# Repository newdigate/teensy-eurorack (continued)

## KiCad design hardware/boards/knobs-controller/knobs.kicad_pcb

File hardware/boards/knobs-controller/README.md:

# Knobs Controller

```
status:
   01 Sept 2019: pcb delivery failure, pcbs re-ordered
   13 Dec 2019: 
     * v1.6: issue with tx/rx connection to mainboard fixed
```
## credits
* this board is based on [Arduino MKR Zero](https://store.arduino.cc/arduino-mkr-zero-i2s-bus-sd-for-sound-music-digital-audio-data) design by Arturo Guadalupi (v5.0)

## build
* build details for knob controller can be found here - [BUILD.md](BUILD.md) 
* BOM can be found here [Bill-of-materials.md](Bill-of-materials.md)

## quick details
An independent rotary encoder and potentiometer breakout board based on Arduino MKR Zero
* SAMD21G18A-MU 32bit micro-controller @ 48 MHz. 
* 4 x 12bit rotary potentiometers
* 3 x RGB Illuminated rotary encoder w/ switch
* Communicates with main-board via serial rx / tx

## objectives
Introducing an intermediate micro-controller (ARM cortex M0 / SAMD21G) 
* reduces complexity of mainboard
* reduces number of anlog and digital pins required by teensy for haptic input (knobs and pots)
* simplyfies and unifies mainboard firmware for 

some firmware will run on the M0 microcontroller to relay input (knob value changes) back to the mainboard and receive commands (eg. to light up RGB rotaries ) via serial TX / RX, 

Number of signal required between main-board and knobs controller is reduced to: +5V, GND, TX, RX; 
## revisions
* v1.5: board size reduced slightly on the right hand side to allow assembly to fit in to a 6U high rack mount unit.
* v1.6: 
  * fixed tx/rx connection
  * moved connector to mainboard out of the way

## todo 
- [ ] change mcu to ATSAMD21G18A-AU (jlc pcb assembly friendly)

## How did this happen?
I want to upgrade the mainboard to using a teensy 4.0 and I don't want to rely on using the pins on the underside of the teensy. 

I started with the schematic of [arduino mkr zero](https://create.arduino.cc/projecthub/products/arduino-mkr-zero) (available from arduino -- [MKRZero-reference.zip](https://content.arduino.cc/assets/MKRZero-reference.zip) as eagle .sch and .brd) and removed components from the circuit which I don't need. I needed to keep the SWD (Serial wire debug) pins on the micro-controller available, so I can upload a bootloader- as the usb connection won't be available until the bootloader is programmed via the 6-pin SWD header.

## Images

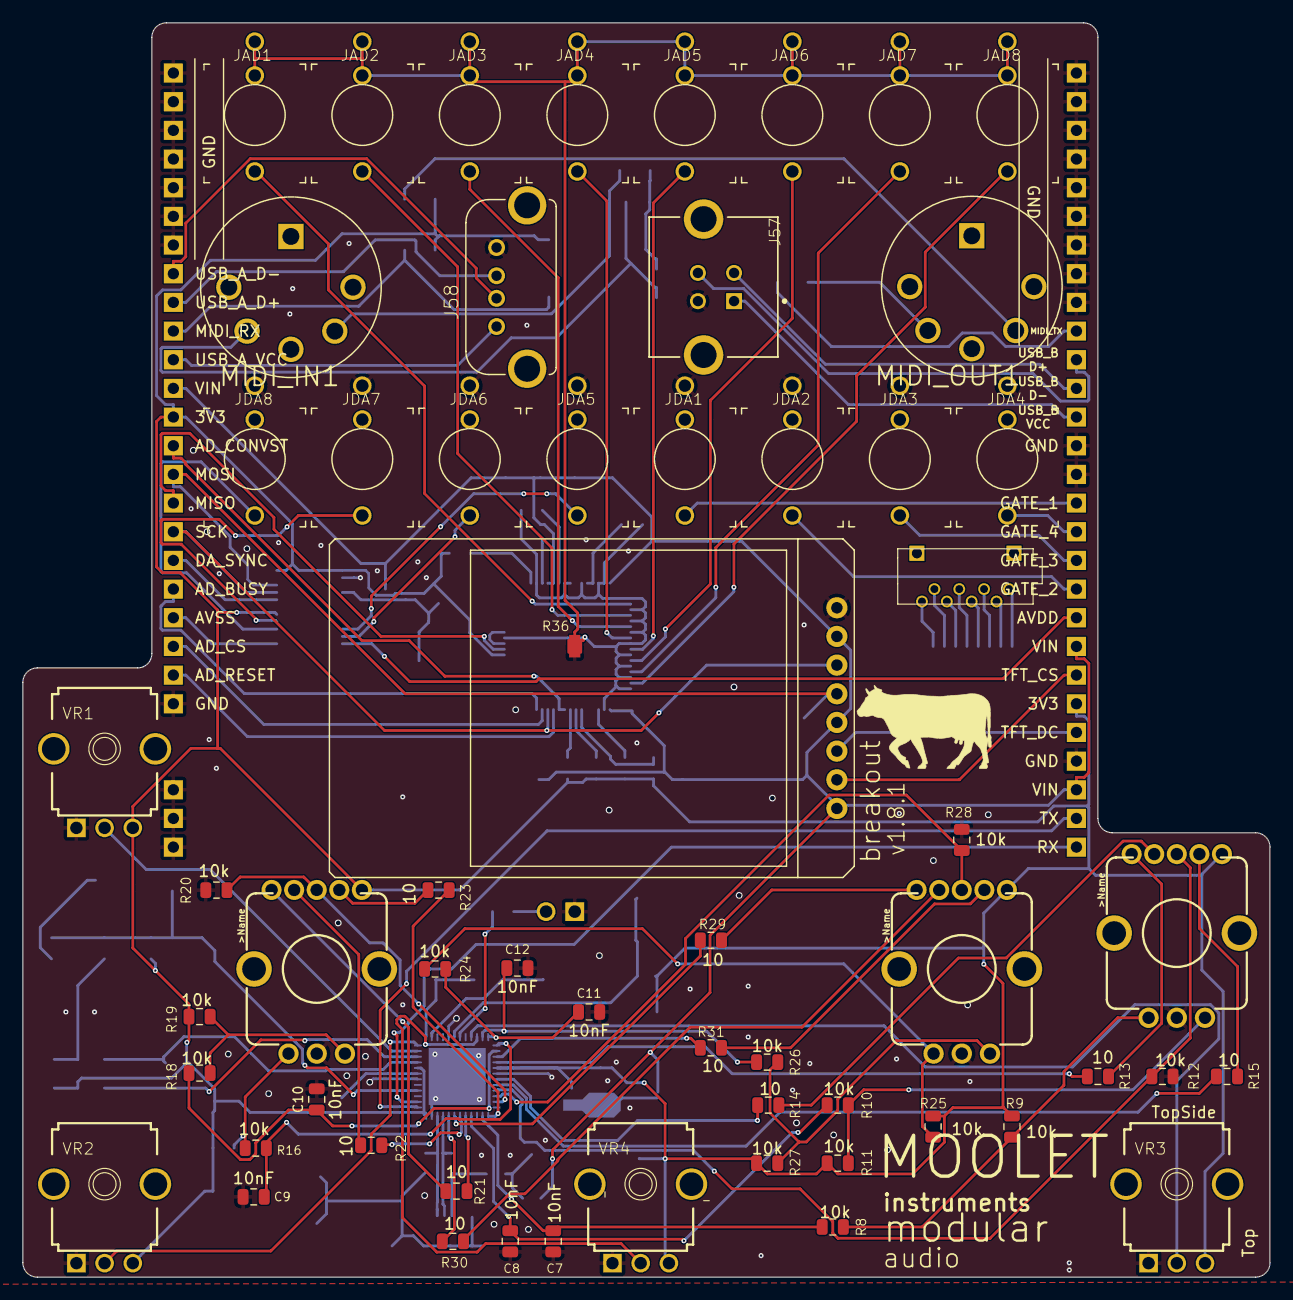
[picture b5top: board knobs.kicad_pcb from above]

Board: 2 copper layers, 110.5 x 111.1 mm, 175 parts (0 on the bottom side), 117 nets.

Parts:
C1: 4.7nF; C_0805_2012Metric
C2, C6: 1nF; C_0805_2012Metric
C3, C13, C15, C16, C17, C21, C22, C23, C24, C28, C29, C30, C31: 0.1uF; C_0805_2012Metric
C4, C5: 20pF; C_0805_2012Metric
C7, C8, C9, C10, C11, C12: 10nF; C_0805_2012Metric
C14, C19, C20, C26, C27: 1uF; C_0805_2012Metric
C18: 4.7uF; C_0805_2012Metric
C25: 10uF; C_0805_2012Metric
D1: PRTR5V0U2X,215; MK1_ZERO_SOT190P230X110-4N
D2: LED; LED_RADIAL_3MM
D3: D; D_0805
F1: MF-FSMF050X-2; MK1_ZERO_0603-F1608X100N
J1: ZX62-AB-5PA(31); MK1_ZERO_USBMICRO-ZX62-AB-5PA
J2: 2X3_SMD_MALE; 2X3_SMT
J3, J4, J5, J6, J7, J8, J9, J10, J11, J12, J13, J14, J15, J16, J17, J18, J19, J20, J21, J22, J23, J24, J25, J26, J27, J28, J29, J30, J31, J32, J33, J34, J35, J36, J37, J38, J39, J40, J41, J42, J43, J44, J45, J46, J47, J48, J49, J50, J51, J52, J53, J54, J55, J56: Conn_01x01_Female; PinSocket_1x01_P2.54mm_Vertical
J57: WURTH_ELECTRONICS_61400413321WURTH_ELECTRONICS_61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; WURTH_ELECTRONICS_61400413321_0
J58: USB-A-S-X-X-VT
J59: ST7735_1.4; ST7735
JAD1, JAD2, JAD3, JAD4, JAD5, JAD6, JAD7, JAD8: THONKICONNNEW; WQP-PJ301M-12_JACK
JDA1, JDA2, JDA3, JDA4, JDA5, JDA6, JDA7, JDA8: THONKICONNNEW; WQP-PJ301M-12_JACK
L1, L2: BLM18PG471SN1D; MK1_ZERO_0603-1608X90N
MIDI_IN1: OG-MIDI_MAB5SHCUI-SD-50BV; OG-MIDI_SD-50BV
MIDI_OUT1: OG-MIDI_MAB5SHCUI-SD-50BV; OG-MIDI_SD-50BV
R1: 1M; R_0805_2012Metric
R2: 39R; R_0805_2012Metric
R3, R6, R7: 330R; R_0805_2012Metric
R4: 1k; R_0805_2012Metric
R5, R8, R9, R10, R11, R12, R16, R17, R18, R19, R20, R24, R25, R26, R27, R28: 10k; R_0805_2012Metric
R13, R14, R15, R21, R22, R23, R29, R30, R31: 10; R_0805_2012Metric
R32, R33, R34, R35, R37: 4.7k; R_0805
R36: 0; NetTie-I_Connected_SMD_small
R38, R39, R40, R41: 220; R_0805_HandSoldering
SW1, SW2, SW3: Rotary Encoder; ENCODER_LED_3_KIT
TP1, TP2, TP3: TEST-POINT3X5; PAD.03X.05
U1: ATSAMD21G18A-48; MK1_ZERO_QFN50P700X700X90-49XN-EPSQ515
U2: AP7215-33YG-13; MK1_ZERO_SOT150P400X160-3N
U3: ANALOG_DEVICES_AD7606BSTZANALOG_DEVICES_AD7606BST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; ANALOG_DEVICES_AD7606BSTZ_2
U4: ANALOG_DEVICES_AD5754BREZANALOG_DEVICES_AD5754BRE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; ANALOG_DEVICES_AD5754BREZ_2
U5: MICROCHIP_MCP1700T-2502E-TTMICROCHIP_MCP1700T-250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; MICROCHIP_MCP1700T-2502E-TT_0
U$1: PUSHBUTTON2; C&K_PTS820_NOPEGS
U$2: YAMAICHI_SD_CARD; YAMAICHI_MICROSD_VERTICAL
U$3: 1734592-8; HFW8R-1STE1LF
U$4: OPTO_DARL_6N138S; 8-SMD
VR1, VR2, VR3, VR4: 50k; MUSICTHINGMODULAR_9MM_SNAP-IN_POT
Y1: 32.768KHz; MK1_ZERO_QUARZO-ABS07

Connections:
+3V3: C13.1, C15.1, C16.1, C20.1, J2.1, J40.1, J41.1, L2.1, R4.2, R5.2, R9.2, R11.1, R17.2, R19.1, R25.2, R27.1, R32.1, R33.1, R34.2, R35.1, R37.2, R38.2, R41.2, SW1.5, SW2.5, SW3.5, U1.17, U1.36, U1.44, U2.3, U3.23, U4.5, U4.11, U4.14, U$4.8, VR1.3, VR2.3, VR3.3, VR4.3
/AD5754 DAC/VREF: C30.1, C31.1, TP3.P$1, U4.17, U5.2
/AD7606/AD_BYTE_SELECT: R33.2, U3.6
/AD7606/AD_OS0: R35.2, U3.3
/AD7606/AD_RANGE: R32.2, U3.8
/AD7606/AD_REFCAP_A: C25.1, U3.44, U3.45
/AD7606/AD_REFSEL: R37.1, U3.34
/AD7606/AD_REGCAP1: C26.1, U3.36
/AD7606/AD_REGCAP2: C27.1, U3.39
/AD7606/AD_STBY: R34.1, U3.7
/FPC connector/SD_CLK: U$2.P$5, U$3.4
/FPC connector/SD_CS: U$2.P$2, U$3.7
/FPC connector/SD_DAT1: U$2.P$8, U$3.1
/FPC connector/SD_DAT2: U$2.P$1, U$3.8
/FPC connector/SD_DATAIN: U$2.P$3, U$3.6
/FPC connector/SD_DATAOUT: U$2.P$7, U$3.2
/FPC connector/SD_GND: U$2.P$6, U$3.3
/FPC connector/SD_VCC: U$2.P$4, U$3.5
/FPC connector/USB_A_D+: J30.1, J58.3
/FPC connector/USB_A_D-: J31.1, J58.2
/FPC connector/USB_A_VCC: J32.1, J58.1
/FPC connector/USB_B_D+: J27.1, J57.3
/FPC connector/USB_B_D-: J28.1, J57.2
/FPC connector/USB_B_VCC: J29.1, J57.1
/knobs_1/PA00_XIN32: C4.2, U1.1, Y1.2
/knobs_1/PA01_XOUT32: C5.2, U1.2, Y1.1
/knobs_1/PA04_AIN4: U1.9, VR3.2
/knobs_1/PA05_AIN5: U1.10, VR4.2
/knobs_1/PA06_AIN6: C12.1, R26.1, U1.11
/knobs_1/PA07_AIN7: C11.1, R24.2, U1.12
/knobs_1/PA08_S0_I2C_SDA: C9.1, R16.2, U1.13
/knobs_1/PA09_S0_I2C_SCL: C10.1, R18.1, U1.14
/knobs_1/PA10_TCC0-W2: R31.2, U1.15
/knobs_1/PA11_TCC0-W3: R13.2, U1.16
/knobs_1/PA12_S2_MOSI: R12.2, SW1.3, U1.21
/knobs_1/PA13_S2_SCK: R28.2, SW3.3, U1.22
/knobs_1/PA14_S2_NSS: R20.2, SW2.3, U1.23
/knobs_1/PA16_S1_MOSI: R23.2, U1.25
/knobs_1/PA17_S1_SCK: C7.1, R8.2, U1.26
/knobs_1/PA19_S1_MISO: C8.1, R10.1, U1.28
/knobs_1/PA20_TCC0-W6: R21.2, U1.29
/knobs_1/PA21_TCC0-W7: R22.2, U1.30
/knobs_1/PA22_TC4-W0: R29.2, U1.31
/knobs_1/PA23_TC4-W1: R30.2, U1.32
/knobs_1/PA30_SWCLK: J2.4, R4.1, U1.45
/knobs_1/PA31_SWDIO: J2.2, U1.46
/knobs_1/PB02_AIN10: U1.47, VR1.2
/knobs_1/PB03_AIN11: U1.48, VR2.2
/knobs_1/PB08_LED: R7.1, U1.7
/knobs_1/PB10_TCC0-W4: R14.2, U1.19
/knobs_1/PB11_TCC0-W5: R15.2, U1.20
/knobs_1/PB22_S5_TX: J5.1, U1.37
/knobs_1/PB23_S5_RX: J4.1, U1.38
/knobs_1/RESETN: C3.1, R2.2, R3.2, R5.1, R6.1, U1.40
/knobs_1/USB_N: D1.3, J1.2, U1.33
/knobs_1/USB_P: D1.2, J1.3, U1.34
AD_AGND: C25.2, C26.2, C27.2, JAD1.P$2_SWITCH, JAD1.P$3_SLEEVE, JAD2.P$2_SWITCH, JAD2.P$3_SLEEVE, JAD3.P$2_SWITCH, JAD3.P$3_SLEEVE, JAD4.P$2_SWITCH, JAD4.P$3_SLEEVE, JAD5.P$2_SWITCH, JAD5.P$3_SLEEVE, JAD6.P$2_SWITCH, JAD6.P$3_SLEEVE, JAD7.P$2_SWITCH, JAD7.P$3_SLEEVE, JAD8.P$2_SWITCH, JAD8.P$3_SLEEVE, R36.2, U3.2, U3.26, U3.35, U3.40, U3.41, U3.43, U3.46, U3.47, U3.50, U3.52, U3.54, U3.56, U3.58, U3.60, U3.62, U3.64
AD_BUSY: J52.1, U3.14
AD_CONVST: J53.1, U3.9, U3.10
AD_CS: J55.1, U3.13
AD_RESET: J54.1, U3.11
AD_V1: JAD1.P$1_TIP, U3.49
AD_V2: JAD2.P$1_TIP, U3.51
AD_V3: JAD3.P$1_TIP, U3.53
AD_V4: JAD4.P$1_TIP, U3.55
AD_V5: JAD5.P$1_TIP, U3.57
AD_V6: JAD6.P$1_TIP, U3.59
AD_V7: JAD7.P$1_TIP, U3.61
AD_V8: JAD8.P$1_TIP, U3.63
AVDD: J46.1, U4.24
AVSS: J47.1, U4.1
DA_SYNC: J36.1, U4.7
DA_V1: JDA8.P$1_TIP, U4.3
DA_V2: JDA7.P$1_TIP, U4.4
DA_V3: JDA6.P$1_TIP, U4.23
DA_V4: JDA5.P$1_TIP, U4.22
GATE_1: J42.1, JDA1.P$1_TIP
GATE_2: J43.1, JDA2.P$1_TIP
GATE_3: J44.1, JDA3.P$1_TIP
GATE_4: J45.1, JDA4.P$1_TIP
GND: C1.2, C2.2, C3.2, C4.1, C5.1, C6.2, C7.2, C8.2, C9.2, C10.2, C11.2, C12.2, C13.2, C14.2, C15.2, C16.2, C17.2, C18.2, C19.2, C20.2, C21.2, C22.2, C23.2, C24.2, C28.2, C29.2, C30.2, C31.2, D2.C, J1.5, J2.5, J3.1, J7.1, J8.1, J9.1, J10.1, J11.1, J12.1, J13.1, J14.1, J15.1, J16.1, J17.1, J18.1, J19.1, J20.1, J21.1, J22.1, J23.1, J24.1, J25.1, J26.1, J37.1, J56.1, J57.4, J58.4, J59.1, JDA1.P$3_SLEEVE, JDA2.P$3_SLEEVE, JDA3.P$3_SLEEVE, JDA4.P$3_SLEEVE, JDA5.P$3_SLEEVE, JDA6.P$3_SLEEVE, JDA7.P$3_SLEEVE, JDA8.P$3_SLEEVE, R1.1, R12.1, R20.1, R28.1, R36.1, SW1.C, SW2.C, SW3.C, U1.5, U1.18, U1.35, U1.42, U1.49, U2.1, U3.4, U3.5, U3.16, U3.17, U3.18, U3.19, U3.20, U3.21, U3.22, U3.25, U3.27, U3.28, U3.29, U3.30, U3.31, U3.32, U3.33, U4.10, U4.15, U4.18, U4.19, U4.20, U4.21, U5.1, U$1.1, U$1.2, U$1.3, U$1.4, U$1.5, U$4.5, VR1.1, VR2.1, VR3.1, VR4.1
MIDI_IN_PIN4: MIDI_IN1.4, R39.1
MIDI_IN_PIN5: D3.2, MIDI_IN1.5, U$4.3
MIDI_OUT_PIN4: MIDI_OUT1.4, R38.1
MIDI_OUT_PIN5: MIDI_OUT1.5, R40.1
MIDI_RX: J33.1, R41.1, U$4.6
MIDI_TX: J34.1, R40.2
unnamed: C1.1, D1.1, J1.6, J1.7, J1.8, J1.9, J1.10, J1.11, R1.2
unnamed: C2.1, F1.1, L1.1
unnamed: C14.1, U1.43
unnamed: C17.1, C18.1, L2.2, U1.6
unnamed: D1.4, F1.2, J1.1
unnamed: D2.A, R7.2
unnamed: D3.1, R39.2, U$4.2
unnamed: J2.3, R2.1
unnamed: R3.1, U$1.6
unnamed: R8.1, R9.1, SW1.A
unnamed: R10.2, R11.2, SW1.B
unnamed: R13.1, SW1.1
unnamed: R14.1, SW1.2
unnamed: R15.1, SW1.4
unnamed: R16.1, R17.1, SW2.A
unnamed: R18.2, R19.2, SW2.B
unnamed: R21.1, SW2.1
unnamed: R22.1, SW2.2
unnamed: R23.1, SW2.4
unnamed: R24.1, R25.1, SW3.A
unnamed: R26.2, R27.2, SW3.B
unnamed: R29.1, SW3.1
unnamed: R30.1, SW3.2
unnamed: R31.1, SW3.4
SPI0_MISO: J51.1, U3.24
SPI0_MOSI: J35.1, J59.4, TP2.P$1, U4.9
SPI0_SCK: J50.1, J59.3, U3.12, U4.8
TFT_CS: J49.1, J59.7
TFT_DC: J48.1, J59.6
VIN: C6.1, C19.1, C21.1, C22.1, C23.1, C24.1, C28.1, C29.1, J6.1, J38.1, J39.1, J59.2, J59.5, J59.8, L1.2, TP1.P$1, U2.2, U3.1, U3.37, U3.38, U3.48, U5.3

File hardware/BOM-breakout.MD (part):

| No | Qty | Reference(s)                                                                                   | Value                                                          | Footprint                     | Mfg. Part Number      |         |        |
|----|-----|------------------------------------------------------------------------------------------------|----------------------------------------------------------------|-------------------------------|-----------------------|---------|--------|
| 1  | 1   | C1                                                                                             | 4.7nF                                                          | 0805                          | C0805V472KDRACTU      | £0.181  | £0.18  |
| 2  | 2   | C2, C6                                                                                         | 1nF                                                            | 0805                          | C0805C102KARACAUTO    | £0.076  | £0.15  |
| 3  | 13  | C3, C13, C15, C16, C17, C21, C22, C23, C24, C28, C29, C30, C31                                 | 0.1uF                                                          | 0805                          | C0805C104J5RACTU      | £0.016  | £0.20  |
| 4  | 2   | C4, C5                                                                                         | 20pF                                                           | 0805                          | 1276-1829-1-ND        | £0.024  | £0.05  |
| 5  | 6   | C7, C8, C9, C10, C11, C12                                                                      | 10nF                                                           | 0805                          | C0805C103J5RACTU      | £0.014  | £0.08  |
| 6  | 5   | C14, C19, C20, C26, C27                                                                        | 1uF                                                            | 0805                          | C0805C105K4RACTU      | £0.027  | £0.14  |
| 7  | 1   | C18                                                                                            | 4.7uF                                                          | 0805                          | TAJP475K016RNJ        | £0.389  | £0.39  |
| 8  | 1   | C25                                                                                            | 10uF                                                           | 0805                          | LMK212ABJ106MG-T      | £0.028  | £0.03  |
| 9  | 1   | D1                                                                                             | PRTR5V0U2X,215                                                 | SOT190P230X110-4N             | PRTR5V0U2X,215        | £0.324  | £0.32  |
| 10 | 1   | D3                                                                                             | D                                                              | 0805                          | TS4148 RYG            | £0.020  | £0.02  |
| 11 | 1   | F1                                                                                             | MF-FSMF050X-2                                                  | 0603                          | MF-FSMF050X-2         | £0.543  | £0.54  |
| 12 | 1   | J1                                                                                             | ZX62-AB-5PA(31)                                                | USBMICRO-ZX62-AB-5PA          | ZX62-AB-5PA(31)       | £0.483  | £0.48  |
| 13 | 1   | J2                                                                                             | 2X3_SMD_MALE                                                   | 2X3_SMT                       | M20-8760342           | £0.239  | £0.24  |
| 14 | 1   | J57                                                                                            | WURTH_ELECTRONICS | 61400413321_0                 | 61400413321           | £0.909  | £0.91  |
| 15 | 1   | J58                                                                                            | USB-A-S-X-X-VT                                                 | USB-A-S-X-X-VT                | USB-A-S-S-W-VT        | £1.618  | £1.62  |
| 16 | 1   | J59                                                                                            | ST7735_1.4                                                     | ST7735                        | TFT ST7735 1.44"      | £2.690  | £2.69  |
| 17 | 16  | JAD1, JAD2, JAD3, JAD4, JAD5, JAD6, JAD7, JAD8, JDA1, JDA2, JDA3, JDA4, JDA5, JDA6, JDA7, JDA8 | THONKICONNNEW                                                  | WQP-PJ301M-12_JACK            | PJ398SM               | £0.298  | £4.76  |
| 18 | 2   | L1, L2                                                                                         | BLM18PG471SN1D                                                 | 0603                          | BLM18PG471SN1D        | £0.036  | £0.07  |
| 19 | 2   | MIDI_IN1, MIDI_OUT1                                                                            | OG-MIDI_MAB5SHCUI-SD-50BV                                      | SD-50BV                       | SD-50BV               | £1.033  | £2.07  |
| 20 | 1   | R1                                                                                             | 1M                                                             | 0805                          | CR0805-JW-105ELFCT-ND | £0.006  | £0.01  |
| 21 | 1   | R2                                                                                             | 39R                                                            | 0805                          | 804-6335              | £0.002  | £0.00  |
| 22 | 3   | R3, R6, R7                                                                                     | 330R                                                           | 0805                          | RMCF0805JT330R        | £0.007  | £0.02  |
| 23 | 1   | R4                                                                                             | 1K                                                             | 0805                          | 804-6449              | £0.002  | £0.00  |
| 24 | 16  | R5, R8, R9, R10, R11, R12, R16, R17, R18, R19, R20, R24, R25, R26, R27, R28                    | 10k                                                            | 0805                          | RR1220P-103-D         | £0.016  | £0.26  |
| 25 | 9   | R13, R14, R15, R21, R22, R23, R29, R30, R31                                                    | 10                                                             | 0805                          | RL1220S-100-F         | £0.135  | £1.21  |
| 26 | 5   | R32, R33, R34, R35, R37                                                                        | 4.7k                                                           | 0805                          | CRCW08054K70FKEAC     | £0.017  | £0.09  |
| 27 | 4   | R38, R39, R40, R41                                                                             | 220                                                            | 0805                          | CRCW0805220RFKEAC     | £0.014  | £0.06  |
| 28 | 3   | SW1, SW2, SW3                                                                                  | Rotary Encoder                                                 | ENCODER_LED_3_KIT             | COM-10982             | £3.250  | £9.75  |
| 29 | 1   | U1                                                                                             | ATSAMD21G18A-48                                                | QFN50P700X700X90-49XN | ATSAMD21G18A-MUT      | £2.370  | £2.37  |
| 30 | 1   | U2                                                                                             | AP7215-33YG-13                                                 | SOT150P400X160-3N             | AP7215-33YG-13DICT-ND | £0.349  | £0.35  |
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
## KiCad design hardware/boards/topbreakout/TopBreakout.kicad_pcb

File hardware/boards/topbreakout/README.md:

# Top breakout board

## Bill-of-materials

| Ref                                | Qnty | Value             | Cmp name           | Footprint                                 |
|------------------------------------|------|-------------------|--------------------|-------------------------------------------|
| C1, C2, C3, C4, C6, C9, C10, C11,  | 8    | 0.1u              | C-EUC0805K         | Capacitor_SMD:C_0805_2012Metric           |
| C5, C7,                            | 2    | 1.0uF             | 1.0UF-1206-50V-10% | Capacitor_SMD:C_0805_2012Metric           |
| C8,                                | 1    | 10uF              | 10UF-1206-6.3V-20% | Capacitor_SMD:C_0805_2012Metric           |
| D1,                                | 1    | D                 | D                  | Diodes_SMD:D_0805                         |
| R2, R5, R1, R3,                    | 4    | 220               | R-US_R0805         | Resistors_SMD:R_0805_HandSoldering        |
| R4, R7, R8, R9, R10,               | 5    | 4.7k              | R-US_R0805         | Resistors_SMD:R_0805                      |
| U1,                                | 1    | AD7606BSTZ        | AD7606BSTZ         | topbreakout:ANALOG_DEVICES_AD7606BSTZ_2   |
| U3,                                | 1    | AD5754BREZ        | AD5754BREZ         | topbreakout:ANALOG_DEVICES_AD5754BREZ_2   |
| U5,                                | 1    | MCP1700T-2502E-TT | MCP1700T-2502E-TT  | topbreakout:MICROCHIP_MCP1700T-2502E-TT_0 |
| U$1,                               | 1    | YAMAICHI_SD_CARD  | YAMAICHI_SD_CARD   | topbreakout:YAMAICHI_MICROSD_VERTICAL     |
| U$2,                               | 1    | 1734592-8         | 1734592-8          | common:HFW8R-1STE1LF                      |
| U$3,                               | 1    | OPTO_DARL_6N138S  | OPTO_DARL_6N138S   | Mainboard:8-SMD                           |

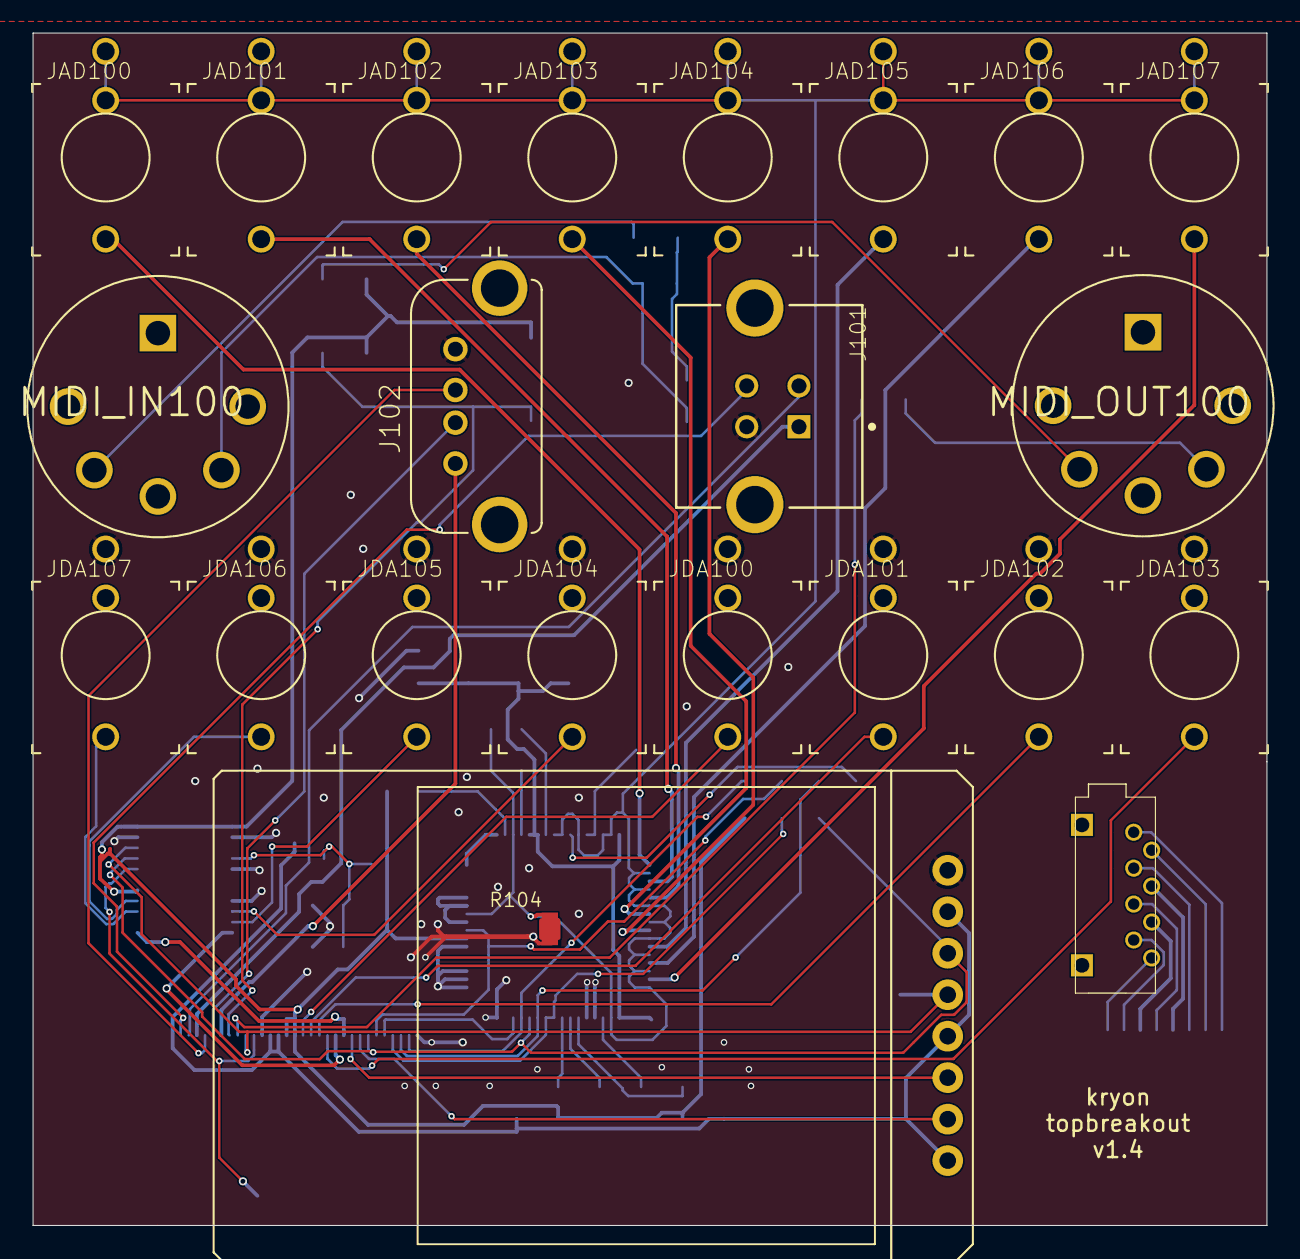
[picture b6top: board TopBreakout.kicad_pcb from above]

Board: 2 copper layers, 75.6 x 73.0 mm, 61 parts (0 on the bottom side), 64 nets.

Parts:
C100, C101, C102, C103: 0.1u; C0805K
C104: 10uF; C_0805_2012Metric
C105, C106: 1.0uF; C_0805_2012Metric
C107, C108: 0.1uF; C_0805
C109, C110: 0.1uF; C_0805_2012Metric
D100: D; D_0805
J100: MOLEX_52892-3033MOLEX_52892-3033_0_0; MOLEX_52892-3033_0
J101: WURTH_ELECTRONICS_61400413321WURTH_ELECTRONICS_61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; WURTH_ELECTRONICS_61400413321_0
J102: USB-A-S-X-X-VT
J103: ST7735_1.4; ST7735
JAD100, JAD101, JAD102, JAD103, JAD104, JAD105, JAD106, JAD107: THONKICONNNEW; WQP-PJ301M-12_JACK
JDA100, JDA101, JDA102, JDA103, JDA104, JDA105, JDA106, JDA107: THONKICONNNEW; WQP-PJ301M-12_JACK
MIDI_IN100: OG-MIDI_MAB5SHCUI-SD-50BV; OG-MIDI_SD-50BV
MIDI_OUT100: OG-MIDI_MAB5SHCUI-SD-50BV; OG-MIDI_SD-50BV
R100, R101, R102, R103, R105: 4.7k; R_0805
R104: 0; NetTie-I_Connected_SMD_small
R106, R107, R108, R109: 220; R_0805_HandSoldering
TP100, TP101, TP102, TP103, TP104, TP105, TP106, TP107, TP108, TP109, TP110: TEST-POINT3X5; PAD.03X.05
U100: ANALOG_DEVICES_AD7606BSTZANALOG_DEVICES_AD7606BST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; ANALOG_DEVICES_AD7606BSTZ_2
U101: ANALOG_DEVICES_AD5754BREZANALOG_DEVICES_AD5754BRE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; ANALOG_DEVICES_AD5754BREZ_2
U102: MICROCHIP_MCP1700T-2502E-TTMICROCHIP_MCP1700T-250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; MICROCHIP_MCP1700T-2502E-TT_0
U$100: YAMAICHI_SD_CARD; YAMAICHI_MICROSD_VERTICAL
U$101: 1734592-8; HFW8R-1STE1LF
U$102: OPTO_DARL_6N138S; 8-SMD

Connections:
+3V3: J100.16, J100.17, R100.1, R101.1, R102.2, R103.1, R105.2, R106.2, R109.2, TP102.P$1, U100.23, U101.5, U101.11, U101.14, U$102.8
/AD5754 DAC/VREF: C109.1, C110.1, TP110.P$1, U101.17, U102.2
/AD7606/AD_BYTE_SELECT: R101.2, U100.6
/AD7606/AD_OS0: R103.2, U100.3
/AD7606/AD_RANGE: R100.2, U100.8
/AD7606/AD_REFCAP_A: C104.1, U100.44, U100.45
/AD7606/AD_REFINOUT: TP107.P$1, U100.42
/AD7606/AD_REFSEL: R105.1, U100.34
/AD7606/AD_REGCAP1: C105.1, U100.36
/AD7606/AD_REGCAP2: C106.1, U100.39
/AD7606/AD_STBY: R102.1, U100.7
/AD7606/AVIN: C100.1, C101.1, C102.1, C103.1, TP100.P$1, U100.1, U100.37, U100.38, U100.48
/FPC connector/SD_CLK: U$100.P$5, U$101.4
/FPC connector/SD_CS: U$100.P$2, U$101.7
/FPC connector/SD_DAT1: U$100.P$8, U$101.1
/FPC connector/SD_DAT2: U$100.P$1, U$101.8
/FPC connector/SD_DATAIN: U$100.P$3, U$101.6
/FPC connector/SD_DATAOUT: U$100.P$7, U$101.2
/FPC connector/SD_GND: U$100.P$6, U$101.3
/FPC connector/SD_VCC: U$100.P$4, U$101.5
/FPC connector/USB_A_D+: J100.27, J102.3
/FPC connector/USB_A_D-: J100.26, J102.2
/FPC connector/USB_A_VCC: J100.25, J102.1
/FPC connector/USB_B_D+: J100.30, J101.3
/FPC connector/USB_B_D-: J100.29, J101.2
/FPC connector/USB_B_VCC: J100.28, J101.1
AD_AGND: C104.2, C105.2, C106.2, JAD100.P$2_SWITCH, JAD100.P$3_SLEEVE, JAD101.P$2_SWITCH, JAD101.P$3_SLEEVE, JAD102.P$2_SWITCH, JAD102.P$3_SLEEVE, JAD103.P$2_SWITCH, JAD103.P$3_SLEEVE, JAD104.P$2_SWITCH, JAD104.P$3_SLEEVE, JAD105.P$2_SWITCH, JAD105.P$3_SLEEVE, JAD106.P$2_SWITCH, JAD106.P$3_SLEEVE, JAD107.P$2_SWITCH, JAD107.P$3_SLEEVE, R104.2, U100.2, U100.26, U100.35, U100.40, U100.41, U100.43, U100.46, U100.47, U100.50, U100.52, U100.54, U100.56, U100.58, U100.60, U100.62, U100.64
AD_BUSY: J100.5, U100.14
AD_CONVST: J100.4, TP104.P$1, U100.9, U100.10
AD_CS: J100.2, TP101.P$1, U100.13
AD_RESET: J100.3, TP105.P$1, U100.11
AD_V1: JAD100.P$1_TIP, U100.49
AD_V2: JAD101.P$1_TIP, U100.51
AD_V3: JAD102.P$1_TIP, U100.53
AD_V4: JAD103.P$1_TIP, U100.55
AD_V5: JAD104.P$1_TIP, U100.57
AD_V6: JAD105.P$1_TIP, U100.59
AD_V7: JAD106.P$1_TIP, U100.61
AD_V8: JAD107.P$1_TIP, U100.63
AVDD: J100.11, U101.24
AVSS: J100.10, U101.1
DA_SYNC: J100.21, TP109.P$1, U101.7
DA_V1: JDA107.P$1_TIP, U101.3
DA_V2: JDA106.P$1_TIP, U101.4
DA_V3: JDA105.P$1_TIP, U101.23
DA_V4: JDA104.P$1_TIP, U101.22
GATE_1: J100.15, JDA100.P$1_TIP
GATE_2: J100.14, JDA101.P$1_TIP
GATE_3: J100.13, JDA102.P$1_TIP
GATE_4: J100.12, JDA103.P$1_TIP
GND: C100.2, C101.2, C102.2, C103.2, C107.2, C108.2, C109.2, C110.2, J100.1, J100.20, J101.4, J102.4, J103.1, JDA100.P$3_SLEEVE, JDA101.P$3_SLEEVE, JDA102.P$3_SLEEVE, JDA103.P$3_SLEEVE, JDA104.P$3_SLEEVE, JDA105.P$3_SLEEVE, JDA106.P$3_SLEEVE, JDA107.P$3_SLEEVE, R104.1, U100.4, U100.5, U100.16, U100.17, U100.18, U100.19, U100.20, U100.21, U100.22, U100.25, U100.27, U100.28, U100.29, U100.30, U100.31, U100.32, U100.33, U101.10, U101.15, U101.18, U101.19, U101.20, U101.21, U102.1, U$102.5
MIDI_IN_PIN4: D100.2, MIDI_IN100.4, U$102.3
MIDI_IN_PIN5: MIDI_IN100.5, R107.1
MIDI_OUT_PIN4: MIDI_OUT100.4, R108.1
MIDI_OUT_PIN5: MIDI_OUT100.5, R106.1
MIDI_RX: J100.24, R109.1, U$102.6
MIDI_TX: J100.23, R108.2
unnamed: D100.1, R107.2, U$102.2
SPI0_MISO: J100.6, TP103.P$1, U100.24
SPI0_MOSI: J100.22, J103.4, TP108.P$1, U101.9
SPI0_SCK: J100.7, J103.3, TP106.P$1, U100.12, U101.8
TFT_CS: J100.8, J103.7
TFT_DC: J100.9, J103.6
VIN: C107.1, C108.1, J100.18, J100.19, J103.2, J103.5, J103.8, U102.3

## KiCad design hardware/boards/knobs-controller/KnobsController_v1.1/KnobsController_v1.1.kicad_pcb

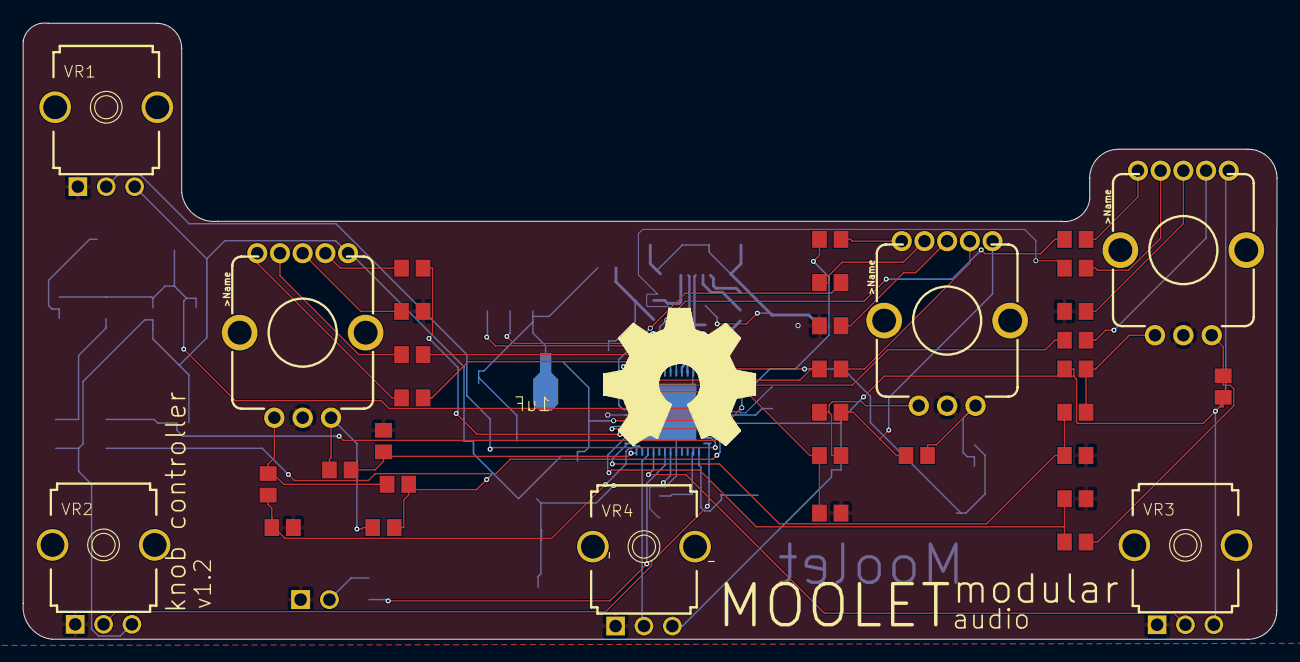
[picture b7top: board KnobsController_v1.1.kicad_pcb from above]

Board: 2 copper layers, 110.5 x 54.3 mm, 71 parts (0 on the bottom side), 61 nets.

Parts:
C4: 1nF; RESISTOR-NICK_C0805
C5: 1nF; RESISTOR-NICK_C1206
C6: 4.7nF; RESISTOR-NICK_C0805
C7: 100nF; C0805
C8, C10, C32: 1uF; RESISTOR-NICK_C0805
C9, C11: 20pF; RESISTOR-NICK_C0805
C19, C28, C29, C30: 100nF; RESISTOR-NICK_C0805
C27: 4.7uF; RESISTOR-NICK_C0805
D1: MK1_ZERO_PRTR5V0U2X,215; MK1_ZERO_SOT190P230X110-4N
D2: LED_LTL-1CHG; LED_RADIAL_3MM
D3: MK1_ZERO_PMEG2005EL; MK1_ZERO_SODFL1008X40N-882D
ENC1:C1, ENC1:C3, ENC2:C1, ENC2:C3, ENC3:C1, ENC3:C3: 10nF; C0805
ENC1:R1, ENC1:R4, ENC1:R5, ENC1:R7, ENC1:R9, ENC2:R1, ENC2:R4, ENC2:R5, ENC2:R7, ENC2:R9, ENC3:R1, ENC3:R4, ENC3:R5, ENC3:R7, ENC3:R9: 10k; R0805
ENC1:R12, ENC1:R13, ENC1:R14, ENC2:R12, ENC2:R13, ENC2:R14, ENC3:R12, ENC3:R13, ENC3:R14: 10; R0805
ENC1:SW1, ENC2:SW1, ENC3:SW1: Rotary Encoder; ENCODER_LED_3_KIT
F2: MK1_ZERO_MF-FSMF050X-2; MK1_ZERO_0603-F1608X100N
J1: ZX62-AB-5PA(31); MK1_ZERO_USBMICRO-ZX62-AB-5PA
J4: JST---S4B-PH-SM4-TB(LF)(SN)_JST_S4B-PH-SM4-TB_LF_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; JST---S4B-PH-SM4-TB(LF)(SN)_JST_S4B-PH-SM4-TB_LF_SN_0
J8: 2X3_SMT
L2, L6: MK1_ZERO_BLM18PG471SN1D; MK1_ZERO_0603-1608X90N
R2: 1M; RESISTOR-NICK_R0805
R7: 1K; R0805
R13, R20: 330R; R0805
R15: 39R; R0805
R16: 10K; R0805
R18: 330R; RESISTOR-NICK_R0805
U2: MK1_ZERO_AP7215-33YG-13; MK1_ZERO_SOT150P400X160-3N
U3: MK1_ZERO_ATSAMD21G18A-48; MK1_ZERO_QFN50P700X700X90-49XN-EPSQ515
U$9: PUSHBUTTON2; C&K_PTS820_NOPEGS
VR1, VR2, VR3, VR4: MUSICTHINGMODULAR_9MM_SNAP-IN_POT
Y1: 32.768KHz; MK1_ZERO_QUARZO-ABS07

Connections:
+3V3: C10.1, C19.1, C28.1, C29.1, ENC1:R4.2, ENC1:R7.1, ENC1:SW1.5, ENC3:R4.2, ENC3:R7.1, ENC3:SW1.5, J8.1, L6.1, R7.2, R16.2, U2.3, U3.17, U3.36, U3.44, VR1.3, VR2.3, VR3.3, VR4.3
ENC1:A: ENC1:R4.1, ENC1:R5.1, ENC1:SW1.A
ENC1:B: ENC1:R7.2, ENC1:R9.2, ENC1:SW1.B
ENC1:BLUE_RAW: ENC1:R14.1, ENC1:SW1.4
ENC1:GREEN_RAW: ENC1:R13.1, ENC1:SW1.2
ENC1:RED_RAW: ENC1:R12.1, ENC1:SW1.1
ENC1:SWITCH: ENC1:R1.2, ENC1:SW1.3
ENC2:3.3V: ENC2:R4.2, ENC2:R7.1, ENC2:SW1.5
ENC2:A: ENC2:R4.1, ENC2:R5.1, ENC2:SW1.A
ENC2:B: ENC2:R7.2, ENC2:R9.2, ENC2:SW1.B
ENC2:BLUE_RAW: ENC2:R14.1, ENC2:SW1.4
ENC2:GREEN_RAW: ENC2:R13.1, ENC2:SW1.2
ENC2:RED_RAW: ENC2:R12.1, ENC2:SW1.1
ENC2:SWITCH: ENC2:R1.2, ENC2:SW1.3
ENC3:A: ENC3:R4.1, ENC3:R5.1, ENC3:SW1.A
ENC3:B: ENC3:R7.2, ENC3:R9.2, ENC3:SW1.B
ENC3:BLUE_RAW: ENC3:R14.1, ENC3:SW1.4
ENC3:GREEN_RAW: ENC3:R13.1, ENC3:SW1.2
ENC3:RED_RAW: ENC3:R12.1, ENC3:SW1.1
ENC3:SWITCH: ENC3:R1.2, ENC3:SW1.3
GND: C4.2, C5.2, C6.2, C7.2, C8.2, C9.1, C10.2, C11.1, C19.2, C27.2, C28.2, C29.2, C30.2, C32.2, D2.C, ENC1:C1.2, ENC1:C3.2, ENC1:R1.1, ENC1:SW1.C, ENC2:C1.2, ENC2:C3.2, ENC2:R1.1, ENC2:SW1.C, ENC3:C1.2, ENC3:C3.2, ENC3:R1.1, ENC3:SW1.C, J1.5, J4.1, J8.5, R2.1, U2.1, U3.5, U3.18, U3.35, U3.42, U3.49, U$9.1, U$9.2, U$9.3, U$9.4, U$9.5, VR1.1, VR2.1, VR3.1, VR4.1
N17650912: D1.4, F2.2, J1.1
N17658775: R13.1, U$9.6
N17852357: C27.1, C30.1, L6.2, U3.6
N17852431: C32.1, U3.43
unnamed: C6.1, D1.1, J1.6, J1.7, J1.8, J1.9, J1.10, J1.11, R2.2
unnamed: C4.1, F2.1, L2.1
unnamed: J8.3, R15.1
unnamed: D2.A, R18.2
PA00_XIN32: C11.2, U3.1, Y1.2
PA01_XOUT32: C9.2, U3.2, Y1.1
PA04_AIN4: U3.9, VR3.2
PA05_AIN5: U3.10, VR4.2
PA06_AIN6: ENC1:C3.1, ENC1:R5.2, U3.11
PA07_AIN7: ENC1:C1.1, ENC1:R9.1, U3.12
PA08_S0_I2C_SDA: ENC3:C3.1, ENC3:R5.2, U3.13
PA09_S0_I2C_SCL: ENC3:C1.1, ENC3:R9.1, U3.14
PA10_TCC0-W2: ENC1:R14.2, U3.15
PA11_TCC0-W3: ENC2:R12.2, U3.16
PA16_S1_MOSI: ENC3:R14.2, U3.25
PA17_S1_SCK: ENC2:C3.1, ENC2:R5.2, U3.26
PA18_USB_ID: D3.A, U3.27
PA19_S1_MISO: ENC2:C1.1, ENC2:R9.1, U3.28
PA20_TCC0-W6: ENC3:R12.2, U3.29
PA21_TCC0-W7: ENC3:R13.2, U3.30
PA22_TC4-W0: ENC1:R12.2, U3.31
PA23_TC4-W1: ENC1:R13.2, U3.32
PA30_SWCLK: J8.4, R7.1, U3.45
PA31_SWDIO: J8.2, U3.46
PB02_AIN10: U3.47, VR1.2
PB03_AIN11: U3.48, VR2.2
PB08_LED: R18.1, U3.7
PB10_TCC0-W4: ENC2:R13.2, U3.19
PB11_TCC0-W5: ENC2:R14.2, U3.20
PB22_S5_TX: J4.2, U3.37
PB23_S5_RX: J4.3, U3.38
RESETN: C7.1, R13.2, R15.2, R16.1, R20.1, U3.40
USB_ID: D3.C, J1.4
USB_N: D1.3, J1.2, U3.33
USB_P: D1.2, J1.3, U3.34
VUSB: C5.1, C8.1, J4.4, L2.2, U2.2

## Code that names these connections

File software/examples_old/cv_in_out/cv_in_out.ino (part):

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#define AD5754R_LOAD                0x50 // Updates the DAC registers and, consequently, the DAC outputs.

#define TFT_SCLK 13  // SCLK can also use pin 14
#define TFT_MOSI 11  // MOSI can also use pin 7
#define TFT_CS   6  // CS & DC can use pins 2, 6, 9, 10, 15, 20, 21, 22, 23
#define TFT_DC    2  //  but certain pairs must NOT be used: 2+10, 6+9, 20+23, 21+22
#define TFT_RST   0 // RST can use any pin
#define SD_CS     4  // CS for SD card, can use any pin
ST7735_t3 TFT = ST7735_t3(TFT_CS, TFT_DC, TFT_MOSI, TFT_SCLK, TFT_RST);

#define SCALE_FACTOR 0.000152587890625
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#define LED 13
#define TOTAL_RAW_BYTES 16

#define TFT_CS 6
#define DA_SYNC 16

int bytesToRead = TOTAL_RAW_BYTES;  
byte raw[TOTAL_RAW_BYTES];  
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uint16_t control_voltage1 = 0x0000;

void setup() {  
  pinMode(DA_SYNC, OUTPUT);
  digitalWrite(DA_SYNC, HIGH); 

  
  pinMode(BUSY, INPUT);
  pinMode(RESET, OUTPUT);
  pinMode(TFT_CS, OUTPUT);
  pinMode(START_CONVERSION, OUTPUT);
  pinMode(CHIP_SELECT, OUTPUT);
  //pinMode(MISO, INPUT);
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
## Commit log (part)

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2020-03-15 gerbers for 1.8.1
2020-03-15 Rename BOM-breakout.md to BOM-breakout.MD
2020-03-15 changed C26 from 4.7uf to 4.7uF, reduce number of distinct parts
2020-03-15 moved files in docs/
2020-03-17 corrected: unconnected trace
2020-03-17 updated silkscreen text
2020-03-17 updated gerbers
2020-03-18 fixed paths to 3d components and footprints
2020-03-20 improve pick n place manual
2020-04-25 change to read midi data from serial3 instead
2020-04-27 added ibom interactive boms
2020-06-15 v1.9 initial schematic, cleanup
2020-06-15 work in progress
2020-06-15 footprints
2020-06-16 pcb w-i-p
2020-06-18 slowly
2020-06-19 pin headers improvements
2020-06-19 single board, rough placement, abt to chop into 2 boards
2020-06-19 placing imprvmts
2020-06-19 schematic improvements
2020-06-20 silkscreen
2020-06-20 silkscreen, corrections
2020-06-20 erc pass
2020-06-22 split into two boards
2020-06-22 mainboard passes drc
2020-06-22 routing improv
2020-06-23 breakout DRC'ed
2020-06-24 minor tweeks to breakout board
2020-06-24 cleanup traces
2020-06-24 silkscreen improvments, gerbers, drc'ed
2020-06-24 images/ readme
2020-06-25 fix merge error
2020-07-22 updated path to boards
2020-07-22 changed schematic from A3 to A4
2020-07-22 repositioned board to middle of page
2020-07-23 schematic A3 -> A4 page
2020-07-23 recenter pcb in page
2020-07-24 test jest-junit annotations action
2020-07-25 docs from latest artifact
2020-07-25 actions: remove annotation step
2020-07-25 connected DAC_SCK output (pin 19) to pin 31, corrected audio out 4 AGND net (was disconnected)
2020-07-25 corrected audio out 4 AGND (was disconnected)
2020-07-25 corrected version number on schematic
2020-07-25 microsd adapter
2020-07-26 corrected TDM rx / tx pins
2020-07-26 remove LRCLK, doesnt seemed to be used, connected LRCLKs to gnd on codec.
2020-07-26 update pcb
2020-07-27 added gerbers for 1.9.1 updates, added uSD extender
2020-07-27 cleanup
2020-07-27 move docs to hardware
2020-07-27 update docs
2020-07-27 add svg of front panel
2020-07-27 add 3d model for acjs-mv5, updated footprint
2020-07-27 updated acjs-mv5 footprints
2020-07-27 update mainboard images
2020-07-27 Revert "recenter pcb in page"
    This reverts commit 40a09dfd2033d5d90cab69f8a1165afd283f11e8.
2020-07-27 corrected edge on breakout board
2020-07-27 images
2020-08-09 correction: re-connect LRCLK to codec - as its required for TDM audio protocol
2020-08-09 pcboard: re-connect LRCLK to codec, move hole for sd-extender cable further away from teensy, and move usb B headers up to avoid collision with SD-extender
2020-08-09 silkscreen improvements
2020-08-09 update revision in schematic
2020-08-10 via sizes corrected
2020-08-10 gerbers updated with correct via size
2020-09-05 fix schematic errors and change breakout to 4 layer board
2020-09-16 updated schematic to latest
2020-09-20 updated breakout board images
2020-09-20 software reset
2020-09-20 01 - control voltate out basic working
2020-09-20 changed status to "in testing"
2020-09-20 basic example using two dacs
2020-11-06 schematic: correct ADC_MISO to MISO1 (pin 39) and DA_SYNC to SPI1 CS (pin 38)
2020-11-06 schematic: correct ADC_RANGE (pin 37)
2020-11-06 schematic: corrections and updates
2020-11-07 schematic, pcb changes for v2.0
2020-11-07 updated version to v2.0
2020-11-07 mainboard: removed loopback for SPI clock as no longer needed
2020-11-15 corrections to breakout pcb
2020-11-28 schematic: change dac bypass caps to polar, correct polarity
2020-11-29 pcb: update polatity of +-12v bypass caps
2020-11-30 schematic: adc to use same external voltage reference as dac
2020-11-30 pcb: update from schematic and route as 4 layer board
2020-11-30 pcb: increase diameter of some via from 0.2mm to 0.25mm for jlcpcb
2020-12-01 pcb: update min via size to .45/.25 mm, routed as 4 layer
2020-12-22 soldermask clearance set to 0.05mm and minimum soldermask bridge to 0.2mm as per jlcpcb
2021-01-09 MAJOR: Correct polarity of +-12V on breakout boardgit add teensy-eurorack-breakout.sch
2021-01-09 MAJOR: breakout PCB correction to polarity of +12V
2021-01-09 Minor pcb improvements: pins of DAC on same net should not bridge if posible as it looks unintentional solder bridge
2021-01-27 Breakout: changed from 4 layer to 2 layer; Mainboard: add serial daisy chain RX/TX to RX4/TX4
2021-01-27 update board images
2021-01-27 fuck facebook
2021-01-30 mainboard pcb: spaced tracks out
2021-01-30 mainboard pcb: minor cleanup
2021-02-13 st7735: change vcc,reset,backlight from 5v to 3v3
2021-02-13 v.2.0.3
2021-02-25 update BOM
2021-02-27 example: simple CV scope
2021-02-27 curve example
2021-02-28 example: audio in -> cv out
2021-03-01 remove ref to DrawingCanvas.h
2021-03-01 audioin -> cvout
2021-03-01 Tie LRCLK pin 20 to pin40 to sync DAC/ADC sampling w/ audio sampling
2021-03-01 Mainboard PCB: Tie LRCLK pin20 to pin40 to sync DAC/ADC sampling w/ audio sampling
2021-03-07 example: audio in -> cv out with 2 simple scopes
2021-03-08 cv input simple scope x 2
2021-03-09 add PIN definitions for TFT display
2021-03-13 refactor examples folder, add PIN definitions for TFT display
2021-03-15 examples
2021-04-03 FIXED: add 1k pull-up resistor to MIDI rx pin
2021-04-03 breakout-board: silkscreen: add Kicad OpenSourceHardware logo
2021-04-03 mainboard-board: silkscreen: add Kicad OpenSourceHardware logo
2021-04-03 update schematics
2021-04-03 updated gerbers to v2.1
2021-04-03 gh-pages initial commit
2021-04-03 Set theme jekyll-theme-cayman
2021-04-03 Set theme jekyll-theme-hacker
2021-04-05 software example updates
2021-05-08 input_output_spi
2021-05-08 examples etc
2021-05-13 start of cleanup...
2021-05-13 examples....
2021-05-13 cleanup...
2021-05-13 build software
2021-05-13 correction...
2021-05-13 PaulStoffregen/Audio.git
2021-05-13 PaulStoffregen/ST7735_t3
2021-05-13 ResponsiveAnalogRead
2021-05-13 arduino_midi_library
2021-05-14 individual builds
2021-05-14 rename workflows
2021-05-14 correction
2021-05-14 corrections
2021-05-15 do not build on commit of .md files
2021-05-15 adding readme for examples, wip
2021-05-15 readme
2021-05-15 turn up the volume
2021-05-15 restructure + add basic mp3
2021-05-15 remove unused variable
2021-05-15 update workflows
2021-05-16 levels example
2021-05-16 analyze all audio channels
2021-05-16 add display levels to build
2021-06-11 pitch example
2021-06-11 toggle antialiasing
2021-07-22 readme: just testing
2021-11-08 Update README.md
    https://forum.kicad.info/t/warning-avoid-all-links-to-kicad-pcb-org-use-kicad-org/31521
2022-11-09 trigger kicad github action...
